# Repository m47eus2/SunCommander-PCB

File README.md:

# SunCommander-PCB

PCB boards for energy optimalization device. Contactors control for power switching with full optical isolation. Multiple current measurments made with current transformers.

## Relay Module
Complete 8 relay module (230V 10A) controlled by I2C with full optical isolation and separate power source for relays coils
- Relay control with full optical isolation (with PC817 optocouplers), separate power sources and LED signalization
- Optocouplers controled by I2C pin expanders (PCF8574N) and inverting digital buffers beetween
- Conntcts to MCU with power supply, I2C bus and buffer enable signal. Requires separate 5V power supply for relays coils control
- High current terminal blocks

## Sensor Module
Helps measuring currents from 10 current transformers
- Connects to MCU with power supply, multiplexers address pins and 2 analog signals from 2 out of 10 choosen current sensors
- Muxing signals from each sensor by two CD4051 analog multiplexers to MCU
- Creates biases for current measurments
- Current transformers jack 3.5mm sockets with custom footprints

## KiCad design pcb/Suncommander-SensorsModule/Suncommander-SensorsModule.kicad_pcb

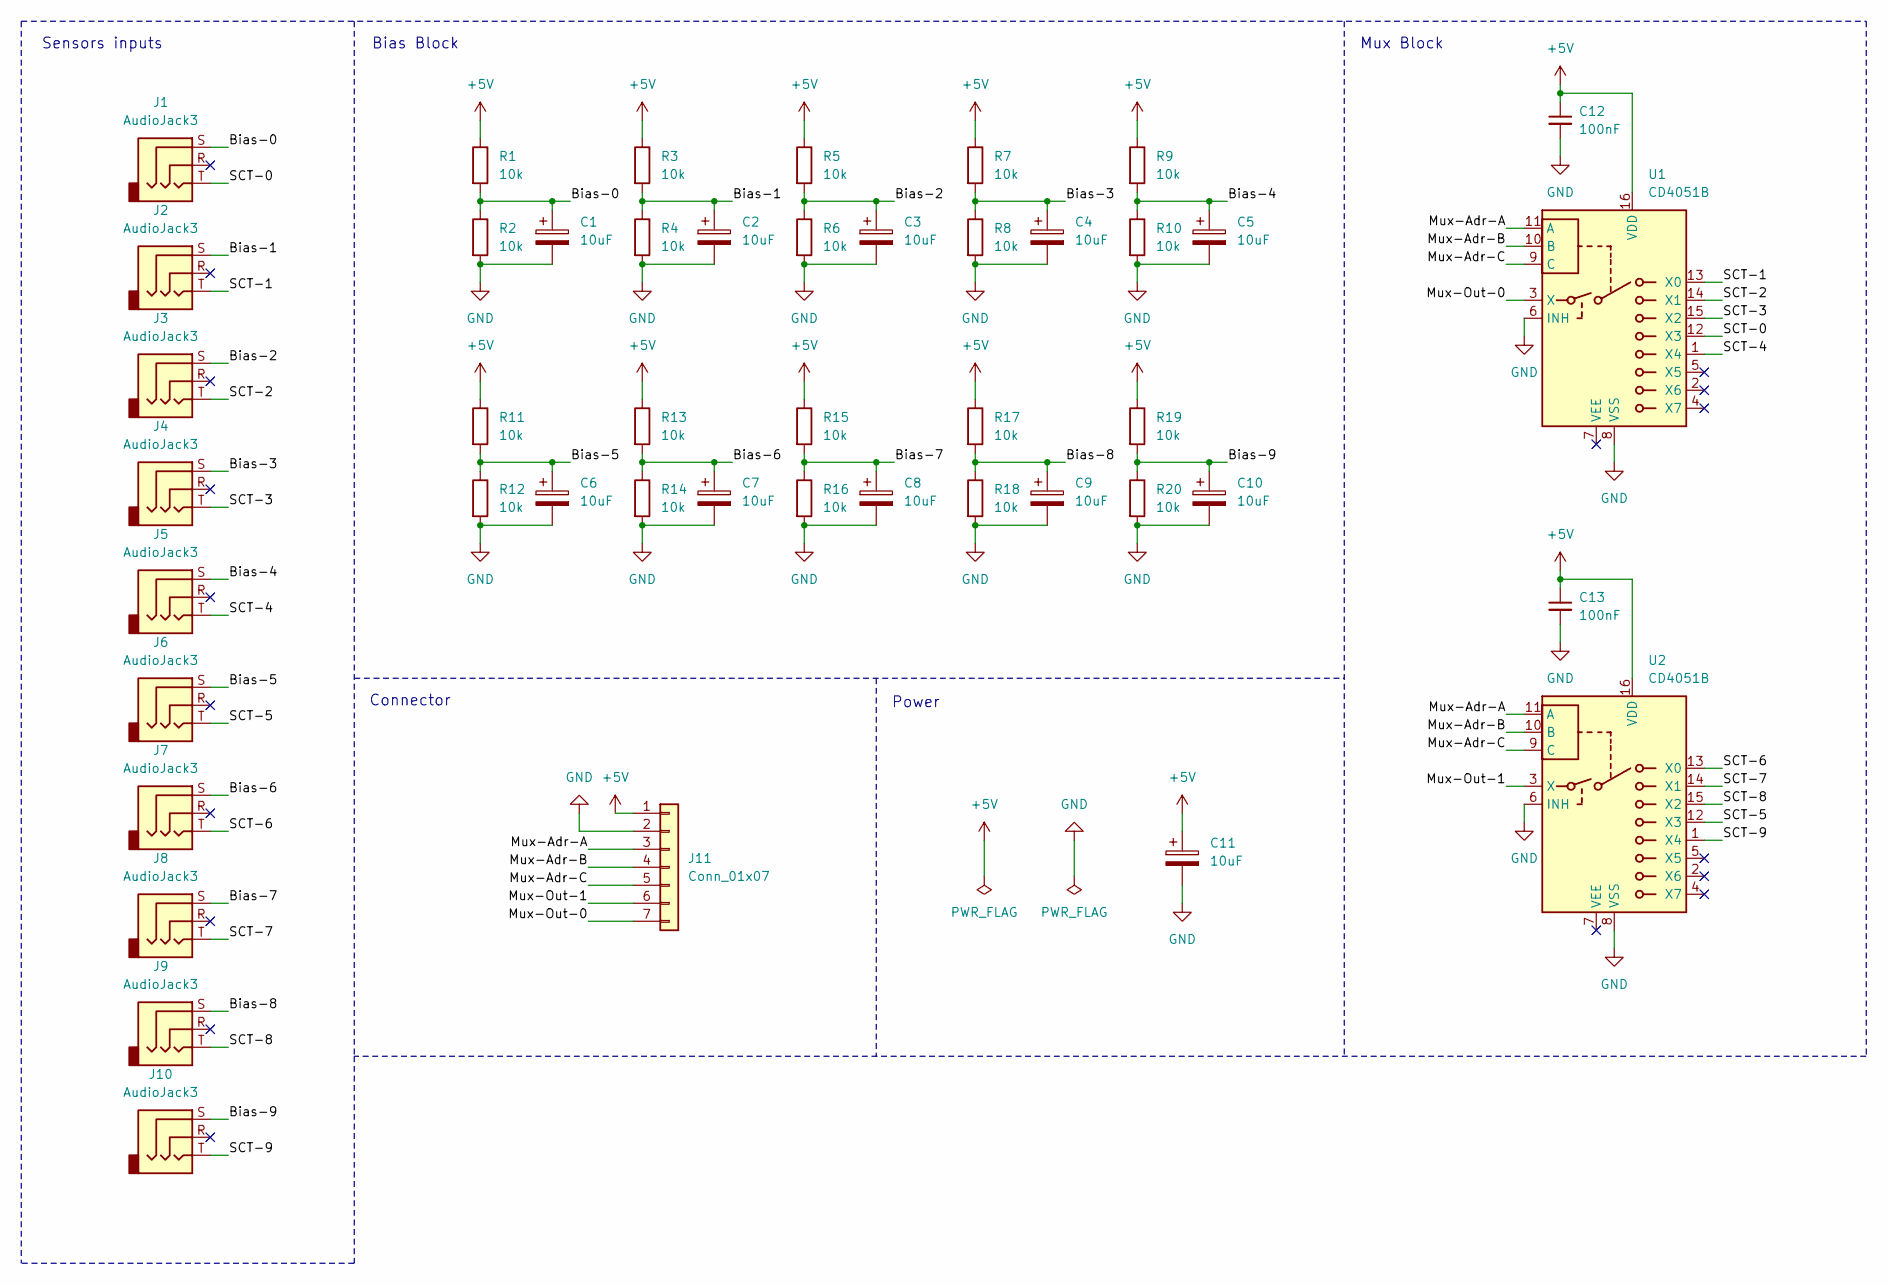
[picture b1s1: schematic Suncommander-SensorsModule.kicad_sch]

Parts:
C1, C2, C3, C4, C5, C6, C7, C8, C9, C10, C11: 10uF; CP_Radial_D5.0mm_P2.00mm
C12, C13: 100nF; C_Disc_D5.0mm_W2.5mm_P2.50mm
J1, J2, J3, J4, J5, J6, J7, J8, J9, J10: AudioJack3; JC-128
J11: Conn_01x07; JST_XH_B7B-XH-A_1x07_P2.50mm_Vertical
R1, R2, R3, R4, R5, R6, R7, R8, R9, R10, R11, R12, R13, R14, R15, R16, R17, R18, R19, R20: 10k; R_Axial_DIN0207_L6.3mm_D2.5mm_P7.62mm_Horizontal
U1, U2: CD4051B; DIP-16_W7.62mm_Socket

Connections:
+5V: C11.1, C12.1, C13.1, J11.1, R1.1, R3.1, R5.1, R7.1, R9.1, R11.1, R13.1, R15.1, R17.1, R19.1, U1.16 (VDD), U2.16 (VDD)
/Bias-0: C1.1, J1.S, R1.2, R2.1
/Bias-1: C2.1, J2.S, R3.2, R4.1
/Bias-2: C3.1, J3.S, R5.2, R6.1
/Bias-3: C4.1, J4.S, R7.2, R8.1
/Bias-4: C5.1, J5.S, R9.2, R10.1
/Bias-5: C6.1, J6.S, R11.2, R12.1
/Bias-6: C7.1, J7.S, R13.2, R14.1
/Bias-7: C8.1, J8.S, R15.2, R16.1
/Bias-8: C9.1, J9.S, R17.2, R18.1
/Bias-9: C10.1, J10.S, R19.2, R20.1
/Mux-Adr-A: J11.3, U1.11 (A), U2.11 (A)
/Mux-Adr-B: J11.4, U1.10 (B), U2.10 (B)
/Mux-Adr-C: J11.5, U1.9 (C), U2.9 (C)
/Mux-Out-0: J11.7, U1.3 (X)
/Mux-Out-1: J11.6, U2.3 (X)
/SCT-0: J1.T, U1.12 (X3)
/SCT-1: J2.T, U1.13 (X0)
/SCT-2: J3.T, U1.14 (X1)
/SCT-3: J4.T, U1.15 (X2)
/SCT-4: J5.T, U1.1 (X4)
/SCT-5: J6.T, U2.12 (X3)
/SCT-6: J7.T, U2.13 (X0)
/SCT-7: J8.T, U2.14 (X1)
/SCT-8: J9.T, U2.15 (X2)
/SCT-9: J10.T, U2.1 (X4)
GND: C1.2, C2.2, C3.2, C4.2, C5.2, C6.2, C7.2, C8.2, C9.2, C10.2, C11.2, C12.2, C13.2, J11.2, R2.2, R4.2, R6.2, R8.2, R10.2, R12.2, R14.2, R16.2, R18.2, R20.2, U1.6 (INH), U1.8 (VSS), U2.6 (INH), U2.8 (VSS)

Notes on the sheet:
Power
Connector
Sensors inputs
Mux Block
Bias Block

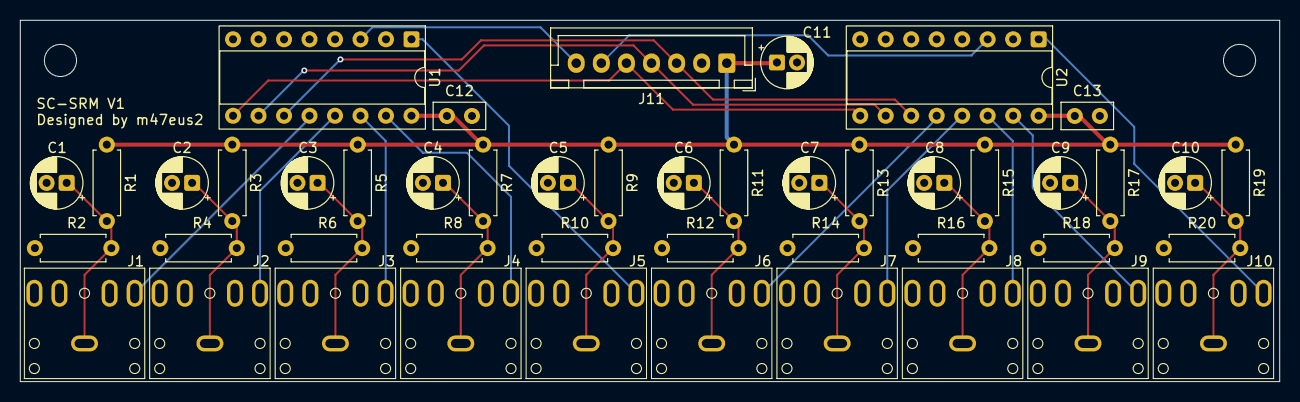
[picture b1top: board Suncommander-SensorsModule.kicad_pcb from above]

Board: 2 copper layers, 125.5 x 36.0 mm, 46 parts (0 on the bottom side), 27 nets.

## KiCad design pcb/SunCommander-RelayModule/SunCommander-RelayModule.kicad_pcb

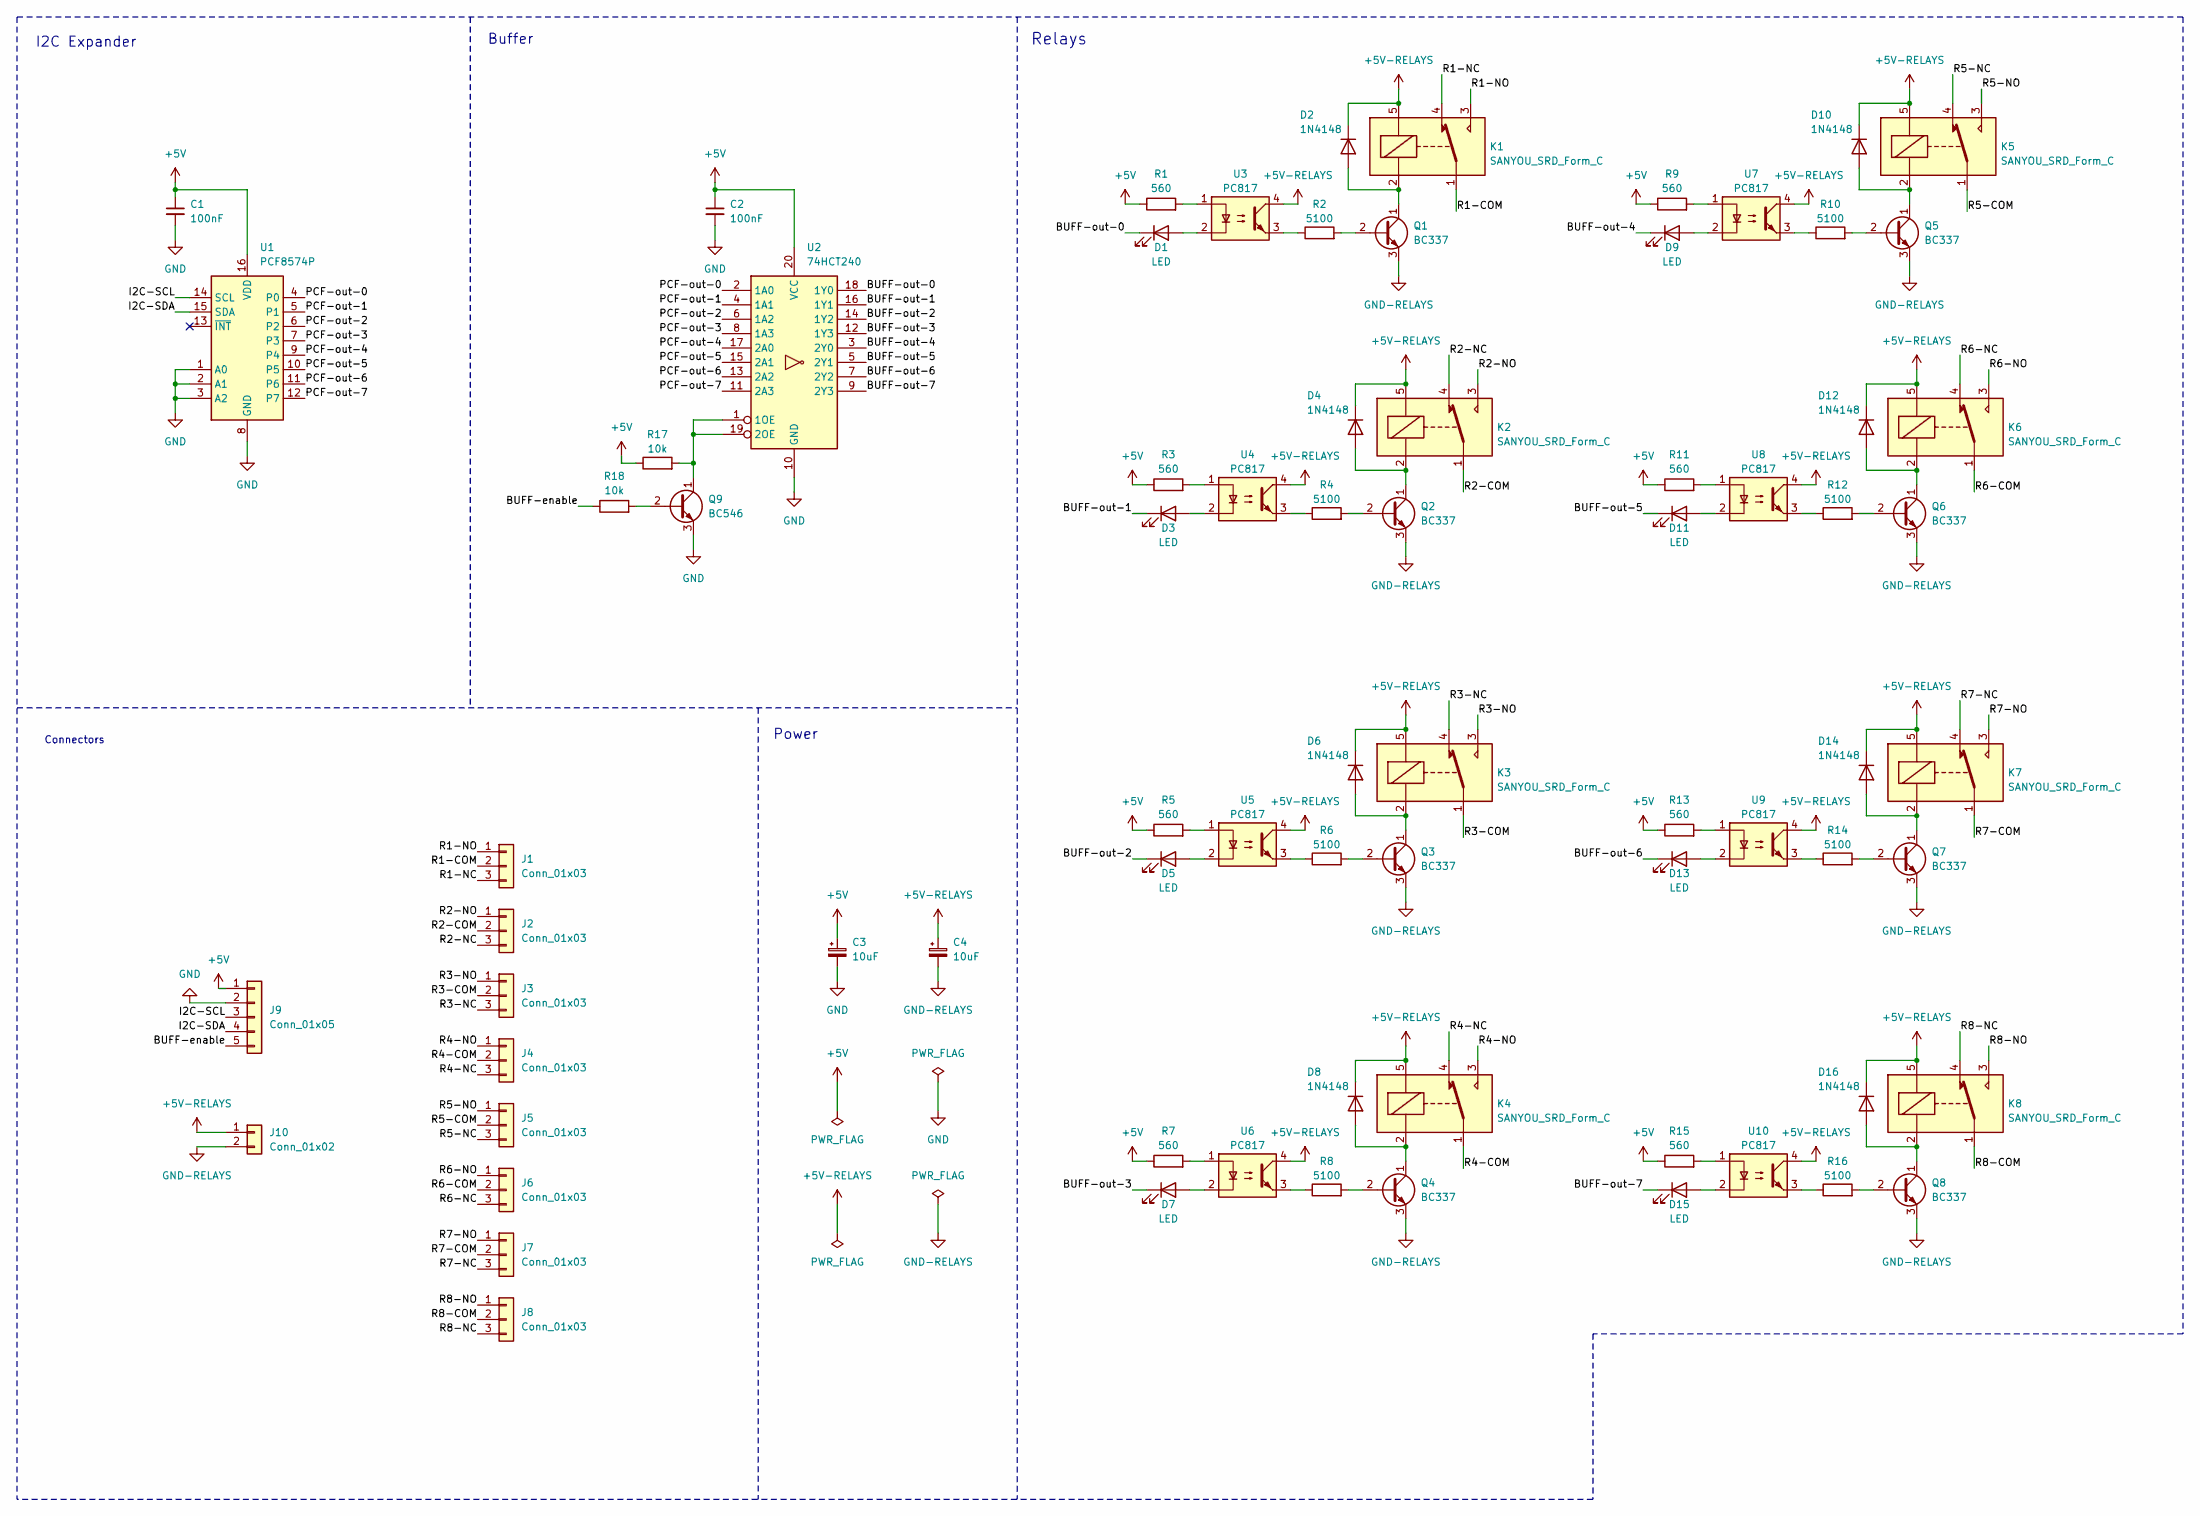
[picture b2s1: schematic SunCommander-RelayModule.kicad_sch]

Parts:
C1, C2: 100nF; C_Disc_D5.0mm_W2.5mm_P2.50mm
C3, C4: 10uF; CP_Radial_D5.0mm_P2.00mm
D1, D3, D5, D7, D9, D11, D13, D15: LED; LED_D5.0mm
D2, D4, D6, D8, D10, D12, D14, D16: 1N4148; D_DO-35_SOD27_P7.62mm_Horizontal
J1, J2, J3, J4, J5, J6, J7, J8: Conn_01x03; TerminalBlock_Phoenix_MKDS-1,5-3_1x03_P5.00mm_Horizontal
J9: Conn_01x05; JST_XH_B5B-XH-A_1x05_P2.50mm_Vertical
J10: Conn_01x02; TerminalBlock_Phoenix_MKDS-1,5-2_1x02_P5.00mm_Horizontal
K1, K2, K3, K4, K5, K6, K7, K8: SANYOU_SRD_Form_C; Relay_SPDT_SANYOU_SRD_Series_Form_C
Q1, Q2, Q3, Q4, Q5, Q6, Q7, Q8: BC337; TO-92_Inline-customPads
Q9: BC546; TO-92_Inline-customPads
R1, R3, R5, R7, R9, R11, R13, R15: 560; R_Axial_DIN0207_L6.3mm_D2.5mm_P7.62mm_Horizontal
R2, R4, R6, R8, R10, R12, R14, R16: 5100; R_Axial_DIN0207_L6.3mm_D2.5mm_P7.62mm_Horizontal
R17, R18: 10k; R_Axial_DIN0207_L6.3mm_D2.5mm_P7.62mm_Horizontal
U1: PCF8574P; DIP-16_W7.62mm_Socket
U2: 74HCT240; DIP-20_W7.62mm_Socket
U3, U4, U5, U6, U7, U8, U9, U10: PC817; DIP-4_W7.62mm

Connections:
+5V: C1.1, C2.1, C3.1, J9.1, R1.1, R3.1, R5.1, R7.1, R9.1, R11.1, R13.1, R15.1, R17.1, U1.16 (VDD), U2.20 (VCC)
+5V-RELAYS: C4.1, D2.1 (K), D4.1 (K), D6.1 (K), D8.1 (K), D10.1 (K), D12.1 (K), D14.1 (K), D16.1 (K), J10.1, K1.5, K2.5, K3.5, K4.5, K5.5, K6.5, K7.5, K8.5, U3.4, U4.4, U5.4, U6.4, U7.4, U8.4, U9.4, U10.4
/BUFF-enable: J9.5, R18.1
/BUFF-out-0: D1.1 (K), U2.18 (1Y0)
/BUFF-out-1: D3.1 (K), U2.16 (1Y1)
/BUFF-out-2: D5.1 (K), U2.14 (1Y2)
/BUFF-out-3: D7.1 (K), U2.12 (1Y3)
/BUFF-out-4: D9.1 (K), U2.3 (2Y0)
/BUFF-out-5: D11.1 (K), U2.5 (2Y1)
/BUFF-out-6: D13.1 (K), U2.7 (2Y2)
/BUFF-out-7: D15.1 (K), U2.9 (2Y3)
/I2C-SCL: J9.3, U1.14 (SCL)
/I2C-SDA: J9.4, U1.15 (SDA)
/PCF-out-0: U1.4 (P0), U2.2 (1A0)
/PCF-out-1: U1.5 (P1), U2.4 (1A1)
/PCF-out-2: U1.6 (P2), U2.6 (1A2)
/PCF-out-3: U1.7 (P3), U2.8 (1A3)
/PCF-out-4: U1.9 (P4), U2.17 (2A0)
/PCF-out-5: U1.10 (P5), U2.15 (2A1)
/PCF-out-6: U1.11 (P6), U2.13 (2A2)
/PCF-out-7: U1.12 (P7), U2.11 (2A3)
/R1-COM: J1.2, K1.1
/R1-NC: J1.3, K1.4
/R1-NO: J1.1, K1.3
/R2-COM: J2.2, K2.1
/R2-NC: J2.3, K2.4
/R2-NO: J2.1, K2.3
/R3-COM: J3.2, K3.1
/R3-NC: J3.3, K3.4
/R3-NO: J3.1, K3.3
/R4-COM: J4.2, K4.1
/R4-NC: J4.3, K4.4
/R4-NO: J4.1, K4.3
/R5-COM: J5.2, K5.1
/R5-NC: J5.3, K5.4
/R5-NO: J5.1, K5.3
/R6-COM: J6.2, K6.1
/R6-NC: J6.3, K6.4
/R6-NO: J6.1, K6.3
/R7-COM: J7.2, K7.1
/R7-NC: J7.3, K7.4
/R7-NO: J7.1, K7.3
/R8-COM: J8.2, K8.1
/R8-NC: J8.3, K8.4
/R8-NO: J8.1, K8.3
GND: C1.2, C2.2, C3.2, J9.2, Q9.3 (E), U1.1 (A0), U1.2 (A1), U1.3 (A2), U1.8 (GND), U2.10 (GND)
GND-RELAYS: C4.2, J10.2, Q1.3 (E), Q2.3 (E), Q3.3 (E), Q4.3 (E), Q5.3 (E), Q6.3 (E), Q7.3 (E), Q8.3 (E)
unnamed: D1.2 (A), U3.2
unnamed: D2.2 (A), K1.2, Q1.1 (C)
unnamed: D3.2 (A), U4.2
unnamed: D4.2 (A), K2.2, Q2.1 (C)
unnamed: D5.2 (A), U5.2
unnamed: D6.2 (A), K3.2, Q3.1 (C)
unnamed: D7.2 (A), U6.2
unnamed: D8.2 (A), K4.2, Q4.1 (C)
unnamed: D9.2 (A), U7.2
unnamed: D10.2 (A), K5.2, Q5.1 (C)
unnamed: D11.2 (A), U8.2
unnamed: D12.2 (A), K6.2, Q6.1 (C)
unnamed: D13.2 (A), U9.2
unnamed: D14.2 (A), K7.2, Q7.1 (C)
unnamed: D15.2 (A), U10.2
unnamed: D16.2 (A), K8.2, Q8.1 (C)
unnamed: Q1.2 (B), R2.2
unnamed: Q2.2 (B), R4.2
unnamed: Q3.2 (B), R6.2
unnamed: Q4.2 (B), R8.2
unnamed: Q5.2 (B), R10.2
unnamed: Q6.2 (B), R12.2
unnamed: Q7.2 (B), R14.2
unnamed: Q8.2 (B), R16.2
unnamed: Q9.2 (B), R18.2
unnamed: Q9.1 (C), R17.2, U2.1 (1OE), U2.19 (2OE)
unnamed: R1.2, U3.1
unnamed: R2.1, U3.3
unnamed: R3.2, U4.1
unnamed: R4.1, U4.3
unnamed: R5.2, U5.1
unnamed: R6.1, U5.3
unnamed: R7.2, U6.1
unnamed: R8.1, U6.3
unnamed: R9.2, U7.1
unnamed: R10.1, U7.3
unnamed: R11.2, U8.1
unnamed: R12.1, U8.3
unnamed: R13.2, U9.1
unnamed: R14.1, U9.3
unnamed: R15.2, U10.1
unnamed: R16.1, U10.3

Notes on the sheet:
Connectors
Buffer
I2C Expander
Power
Relays

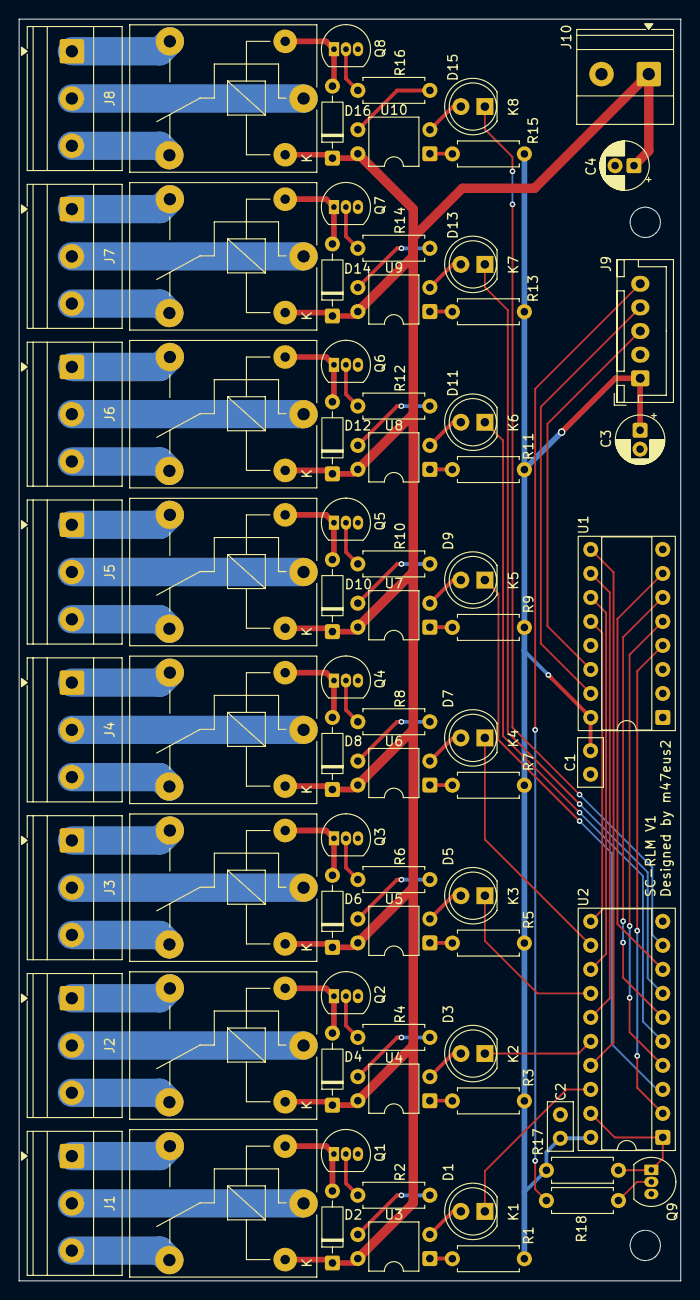
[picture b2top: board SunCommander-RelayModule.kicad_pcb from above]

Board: 2 copper layers, 70.0 x 133.5 mm, 75 parts (0 on the bottom side), 89 nets.

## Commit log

2026-03-05 Adding KiCad projects
2026-03-05 Adding docs
